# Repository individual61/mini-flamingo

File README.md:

# mini-flamingo
ATTiny85 driver for APA102C RGB LEDs w/3 buttons &amp; ISP header.

OSHPark PCB available [here](https://oshpark.com/shared_projects/DTkf5zQz)

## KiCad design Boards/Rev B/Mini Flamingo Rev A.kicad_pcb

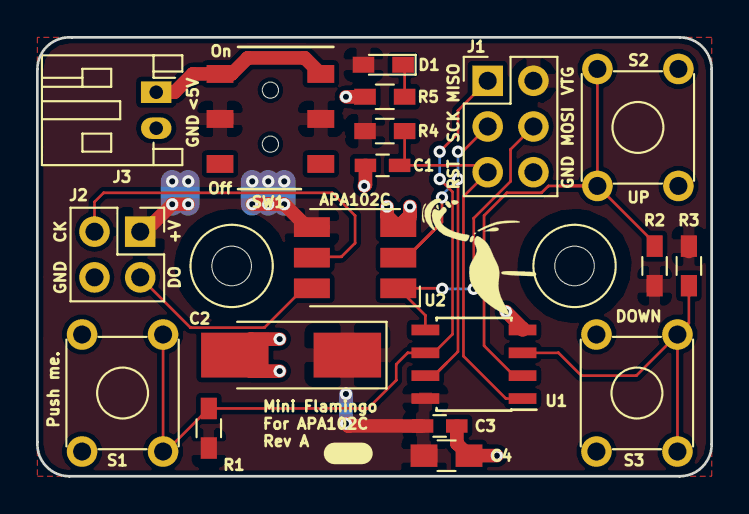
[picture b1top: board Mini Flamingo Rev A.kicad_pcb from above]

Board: 2 copper layers, 37.5 x 24.4 mm, 21 parts (0 on the bottom side), 12 nets.

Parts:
C1, C3: 0.1uF; C_0603_HandSoldering
C2: 100uF; CP_Tantalum_Case-C_EIA-6032-28_Hand
C4: 10uF; C_0805_HandSoldering
D1: Power LED; LED_0603_HandSoldering
Hole1, Hole1#2: 1pin
J1: ISP_Header; Pin_Header_Straight_2x03_Pitch2.54mm
J2: APA102C Out; Pin_Header_Straight_2x02_Pitch2.54mm
J3: Batt Conn; JST_PH_S2B-PH-K_02x2.00mm_Angled
R1, R2, R3: 10k; R_0603_HandSoldering
R4: 4.7k; R_0603_HandSoldering
R5: 1.5k; R_0603_HandSoldering
S1: Cycle; SW_TH_Tactile_Omron_B3F-10xx
S2: Up; SW_TH_Tactile_Omron_B3F-10xx
S3: Down; SW_TH_Tactile_Omron_B3F-10xx
SW1: Power Switch; E-Switch_EG1390
U1: ATTINY85-20SU; SOIC-8_3.9x4.9mm_Pitch1.27mm
U2: APA102C; LED_RGB_5050-6

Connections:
+BATT: C2.1, C3.1, C4.1, D1.2, J1.2, J2.1, R1.1, R2.1, R3.1, R4.1, SW1.2, SW1.5, U1.8, U2.4
/ClockOut: J2.3, U2.5
/DataOut: J2.2, U2.6
/MOSI/WS2812Data: J1.4, U1.5, U2.1
/PIN2/SW2: R2.2, S2.1, S2.2, U1.2
/PIN3/SW3: R3.2, S3.1, S3.2, U1.3
/PIN6/SW1: J1.1, R1.2, S1.1, S1.2, U1.6
/SCK/WS2812Clock: J1.3, U1.7, U2.2
GND: C1.2, C2.2, C3.2, C4.2, J1.6, J2.4, J3.2, R5.2, S1.3, S1.4, S2.3, S2.4, S3.3, S3.4, U1.4, U2.3
unnamed: C1.1, J1.5, R4.2, U1.1
unnamed: D1.1, R5.1
unnamed: J3.1, SW1.1, SW1.4

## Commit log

2018-01-16 Rev A final version as sent to fab
    Had to change some parts so I could place the entire order on Digikey
    (save for the APA102C).
2018-01-16 Rev B initial commit
    No changes from Rev A as sent to fab
2018-01-18 Added Order BOM file
2018-01-22 Mini Flamingo test code and Rev A fixes
2018-01-23 First Rev A test code and added Rev A blue wire to Rev B
    There were two +BAT pours that were not connected. They are now
    connected with a via.
    The forum suggests removing C1; I will consider this for Rev B.
